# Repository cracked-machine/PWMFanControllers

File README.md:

## PWM Fan Controllers

Non-MCU PWM Fan controllers

### 2-Wire Fan Controller

- Ring Oscillator PWM controller
- 9V input (center positive)
- Voltage booster to 12V

[Schematic](2WireFanPWMHexDriverWith9VBoost12V/doc/Schematic/2WireFanPWMHexDriverWith9VBoost12V.pdf)

### Basic 4-Wire Fan Controller

[Schematic](4WireFanPWMHexDriver/doc/4WireFanPWMHexDriver.pdf)

### 4-Wire Fan Controller

- Ring Oscillator PWM controller
- 9V input (center positive)
- Voltage booster to 12V

[Schematic](4WireFanPWMHexDriverWith9VBoost12V/doc/Schematic/4WireFanPWMHexDriverWith9VBoost12V.pdf)

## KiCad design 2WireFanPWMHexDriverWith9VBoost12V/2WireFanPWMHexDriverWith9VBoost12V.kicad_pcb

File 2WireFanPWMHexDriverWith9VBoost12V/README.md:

# 4WireFanPWMHexDriverWith9VBoost12V

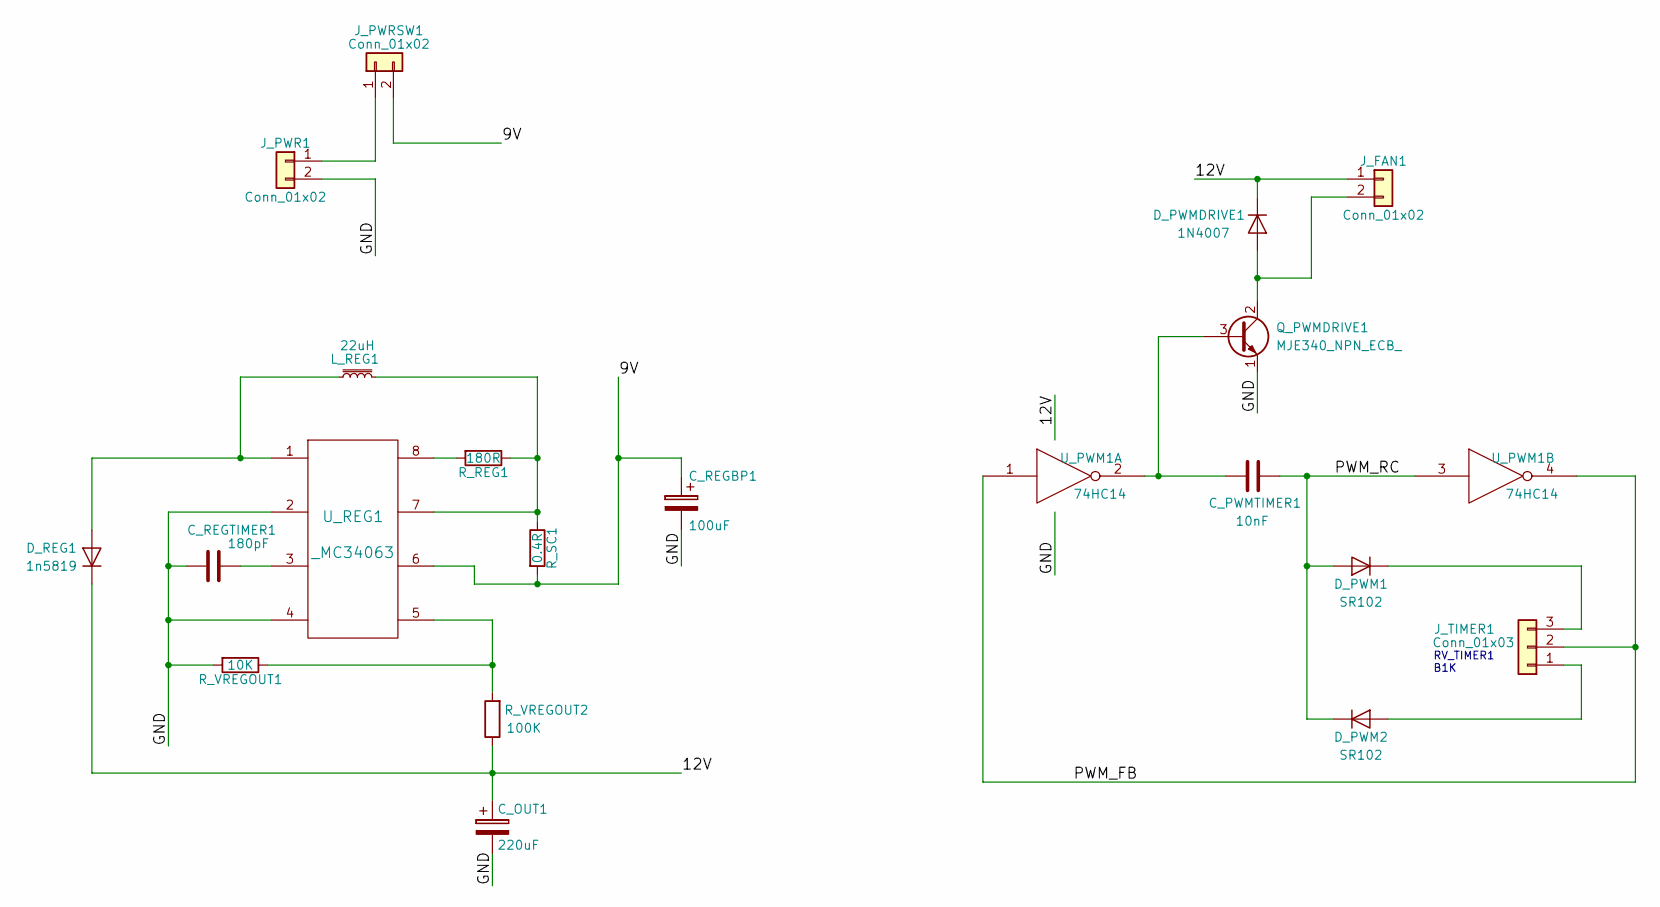
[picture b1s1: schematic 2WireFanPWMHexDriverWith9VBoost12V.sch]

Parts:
C_OUT1: 220uF; CP_Radial_D5.0mm_P2.50mm
C_PWMTIMER1: 10nF; C_Rect_L7_W2.5_P5
C_REGBP1: 100uF; CP_Radial_D5.0mm_P2.50mm
C_REGTIMER1: 180pF; C_Disc_D3.0mm_W1.6mm_P2.50mm
D_PWM1, D_PWM2: SR102; Diode_DO-41_SOD81_Horizontal_RM10
D_PWMDRIVE1: 1N4007; Diode_DO-41_SOD81_Horizontal_RM10
D_REG1: 1n5819; Diode_DO-41_SOD81_Horizontal_RM10
J_FAN1: Conn_01x02; Pin_Header_Straight_1x02_Pitch2.54mm
J_PWR1: Conn_01x02; Pin_Header_Straight_1x02_Pitch2.54mm
J_PWRSW1: Conn_01x02; Pin_Header_Straight_1x02_Pitch2.54mm
J_TIMER1: Conn_01x03; Pin_Header_Straight_1x03_Pitch2.54mm
L_REG1: 22uH; L_Radial_D7.5mm_P5.00mm_Fastron_07P
Q_PWMDRIVE1: MJE340_NPN_ECB_; TO-220_Neutral123_Vertical
R_REG1: 180R; R_Axial_DIN0207_L6.3mm_D2.5mm_P7.62mm_Horizontal
R_SC1: 0.4R; R_Axial_DIN0207_L6.3mm_D2.5mm_P7.62mm_Horizontal
R_VREGOUT1: 10K; R_Axial_DIN0207_L6.3mm_D2.5mm_P7.62mm_Horizontal
R_VREGOUT2: 100K; R_Axial_DIN0207_L6.3mm_D2.5mm_P7.62mm_Horizontal
U_PWM1: 74HC14; DIP-14_W7.62mm_Socket
U_REG1: _MC34063; DIP-8_W7.62mm_Socket_LongPads

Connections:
/9V: C_REGBP1.1, J_PWRSW1.2, R_SC1.2, U_REG1.6
/12V: C_OUT1.1, D_PWMDRIVE1.1 (K), D_REG1.1 (K), J_FAN1.1, R_VREGOUT2.1, U_PWM1.14 (VCC)
/GND: C_OUT1.2, C_REGBP1.2, C_REGTIMER1.2, J_PWR1.2, Q_PWMDRIVE1.1 (E), R_VREGOUT1.2, U_PWM1.7 (GND), U_REG1.2, U_REG1.4
/PWM_FB: J_TIMER1.2, U_PWM1.1, U_PWM1.4
/PWM_RC: C_PWMTIMER1.1, D_PWM1.2 (A), D_PWM2.1 (K), U_PWM1.3
unnamed: C_PWMTIMER1.2, Q_PWMDRIVE1.3 (B), U_PWM1.2
unnamed: C_REGTIMER1.1, U_REG1.3
unnamed: D_PWM1.1 (K), J_TIMER1.3
unnamed: D_PWM2.2 (A), J_TIMER1.1
unnamed: D_PWMDRIVE1.2 (A), J_FAN1.2, Q_PWMDRIVE1.2 (C)
unnamed: D_REG1.2 (A), L_REG1.1, U_REG1.1
unnamed: J_PWR1.1, J_PWRSW1.1
unnamed: L_REG1.2, R_REG1.1, R_SC1.1, U_REG1.7
unnamed: R_REG1.2, U_REG1.8
unnamed: R_VREGOUT1.1, R_VREGOUT2.2, U_REG1.5

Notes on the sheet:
RV_TIMER1 B1K

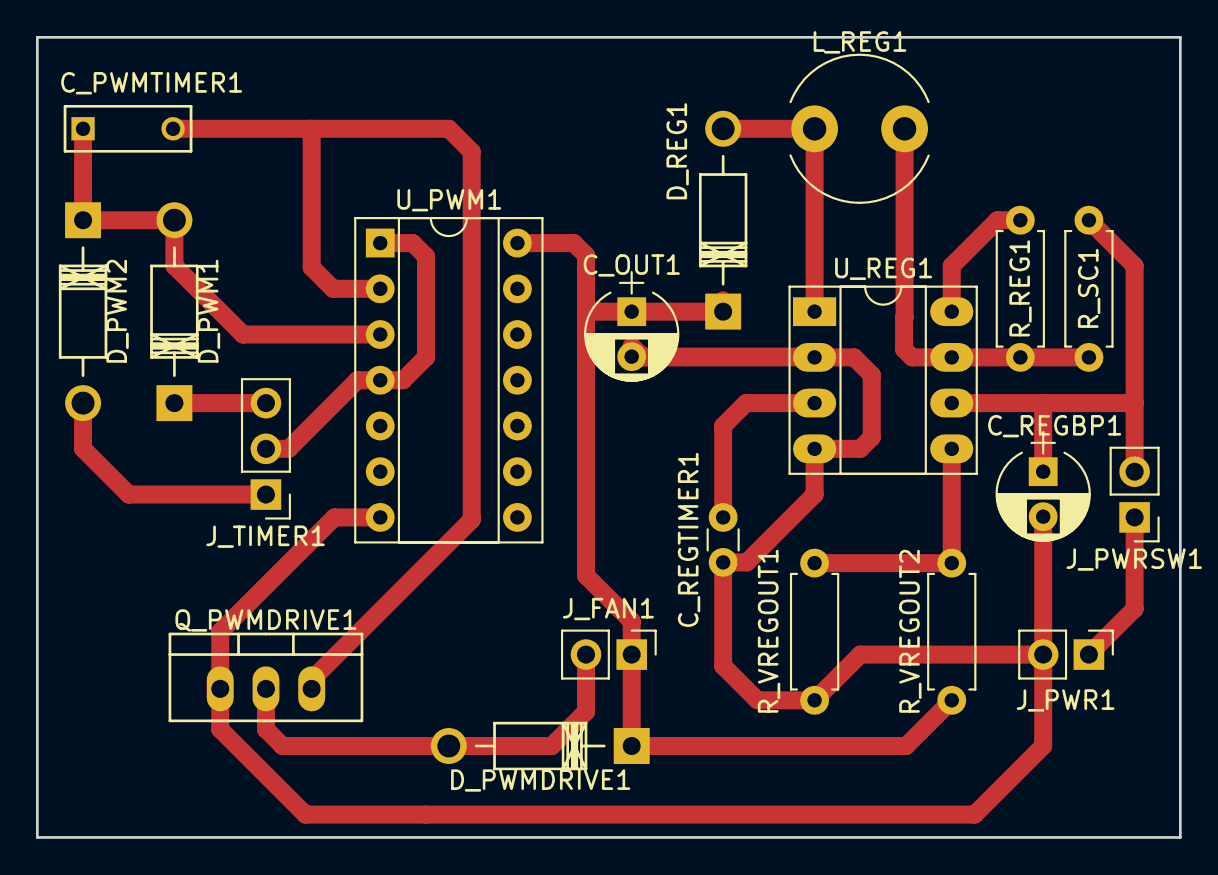
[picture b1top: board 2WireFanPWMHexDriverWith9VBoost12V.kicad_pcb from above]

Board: 2 copper layers, 63.5 x 44.5 mm, 20 parts (0 on the bottom side), 15 nets.

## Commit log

2018-12-02 Multiple projects consolidated
